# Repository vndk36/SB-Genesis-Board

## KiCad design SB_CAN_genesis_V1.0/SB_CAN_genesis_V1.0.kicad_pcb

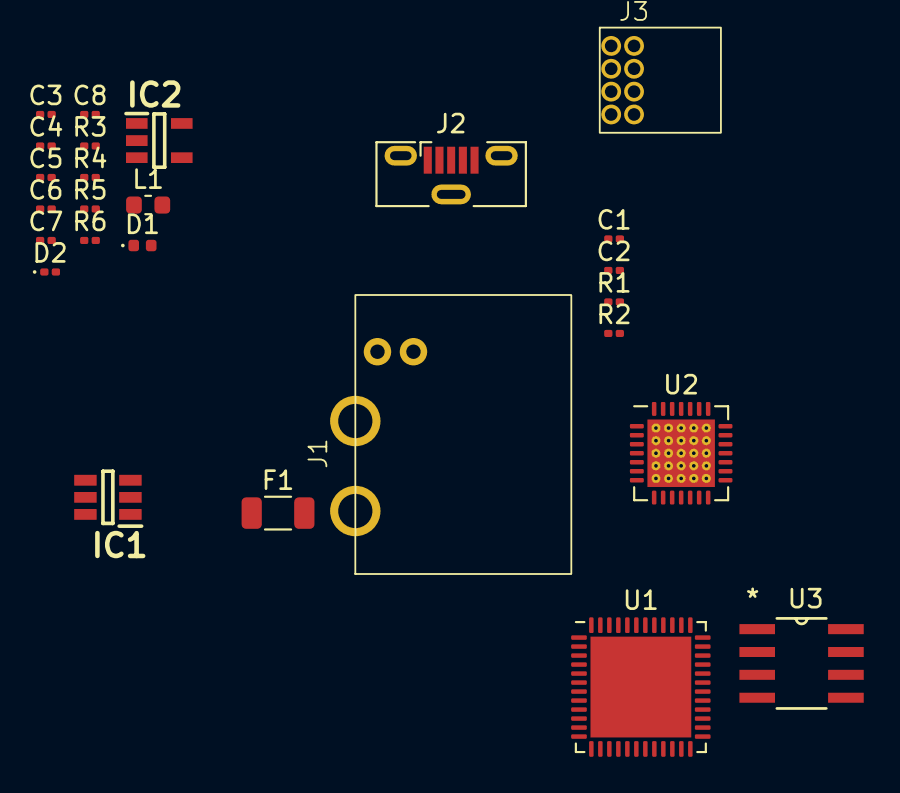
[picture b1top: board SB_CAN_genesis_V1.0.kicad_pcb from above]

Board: 2 copper layers, 26 parts (0 on the bottom side), 10 nets, no tracks yet.

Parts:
C1: 10uF; C_0201_0603Metric
C2, C3: 0.1uF; C_0201_0603Metric
C4, C5: 22uF; C_0201_0603Metric
C6: 75pF; C_0201_0603Metric
C7, C8: 1uF; C_0201_0603Metric
D1: LED; LED_0402_1005Metric
D2: D_Schottky; D_0201_0603Metric
F1: R_1206_3216Metric
IC1: TPS54302DDCR; SOT95P280X110-6N
IC2: AP2112K-3.3TRG1; SOT95P282X130-5N
J1: XT30PW(2+2)-M
J2: USB_B_Micro; USB_Micro-B_Molex-105133-0001
J3: 1.27mm 4x2 header F
L1: 10uH; L_0603_1608Metric
R1: 551K; R_0201_0603Metric
R2: 105K; R_0201_0603Metric
R3: 49.9R; R_0201_0603Metric
R4: 100K; R_0201_0603Metric
R5: 13.3K; R_0201_0603Metric
R6: 1K; R_0201_0603Metric
U1: STM32F072CBUx; QFN-48-1EP_7x7mm_P0.5mm_EP5.6x5.6mm
U2: TMC2209-LA-T; QFN-28-1EP_5x5mm_P0.5mm_EP3.75x3.75mm_ThermalVias
U3: SN65HVD230DR; D8

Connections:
GNDREF: C1.2, C2.2, C4.1, C5.1, C7.1, C8.1, D1.1 (K), D2.2 (A), IC1.1 (GND), IC2.2 (GND), R2.2, R5.2
unnamed: C6.2, R3.2, R4.1
unnamed: D1.2 (A), R6.2
unnamed: C3.1, IC1.6 (BOOT)
unnamed: IC1.5 (EN), R1.2, R2.1
unnamed: C6.1, IC1.4 (FB), R4.2, R5.1
unnamed: C3.2, IC1.2 (SW), L1.1
unnamed: F1.2, J1.1 (VCC)
unnamed: U1.23 (VSS), U1.35 (VSS), U1.47 (VSS), U1.49 (VSS)
VCC: C1.1, C2.1, C4.2, C5.2, C7.2, C8.2, D2.1 (K), F1.1, IC1.3 (VIN), IC2.1 (VIN), IC2.3 (EN), IC2.5 (VOUT), L1.2, R1.1, R3.1, R6.1

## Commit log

2023-08-09 Initial V1.0 board commit not finished yet
2023-08-12 Add new parts for the board
2023-11-11 add datasheet and base board pdf
